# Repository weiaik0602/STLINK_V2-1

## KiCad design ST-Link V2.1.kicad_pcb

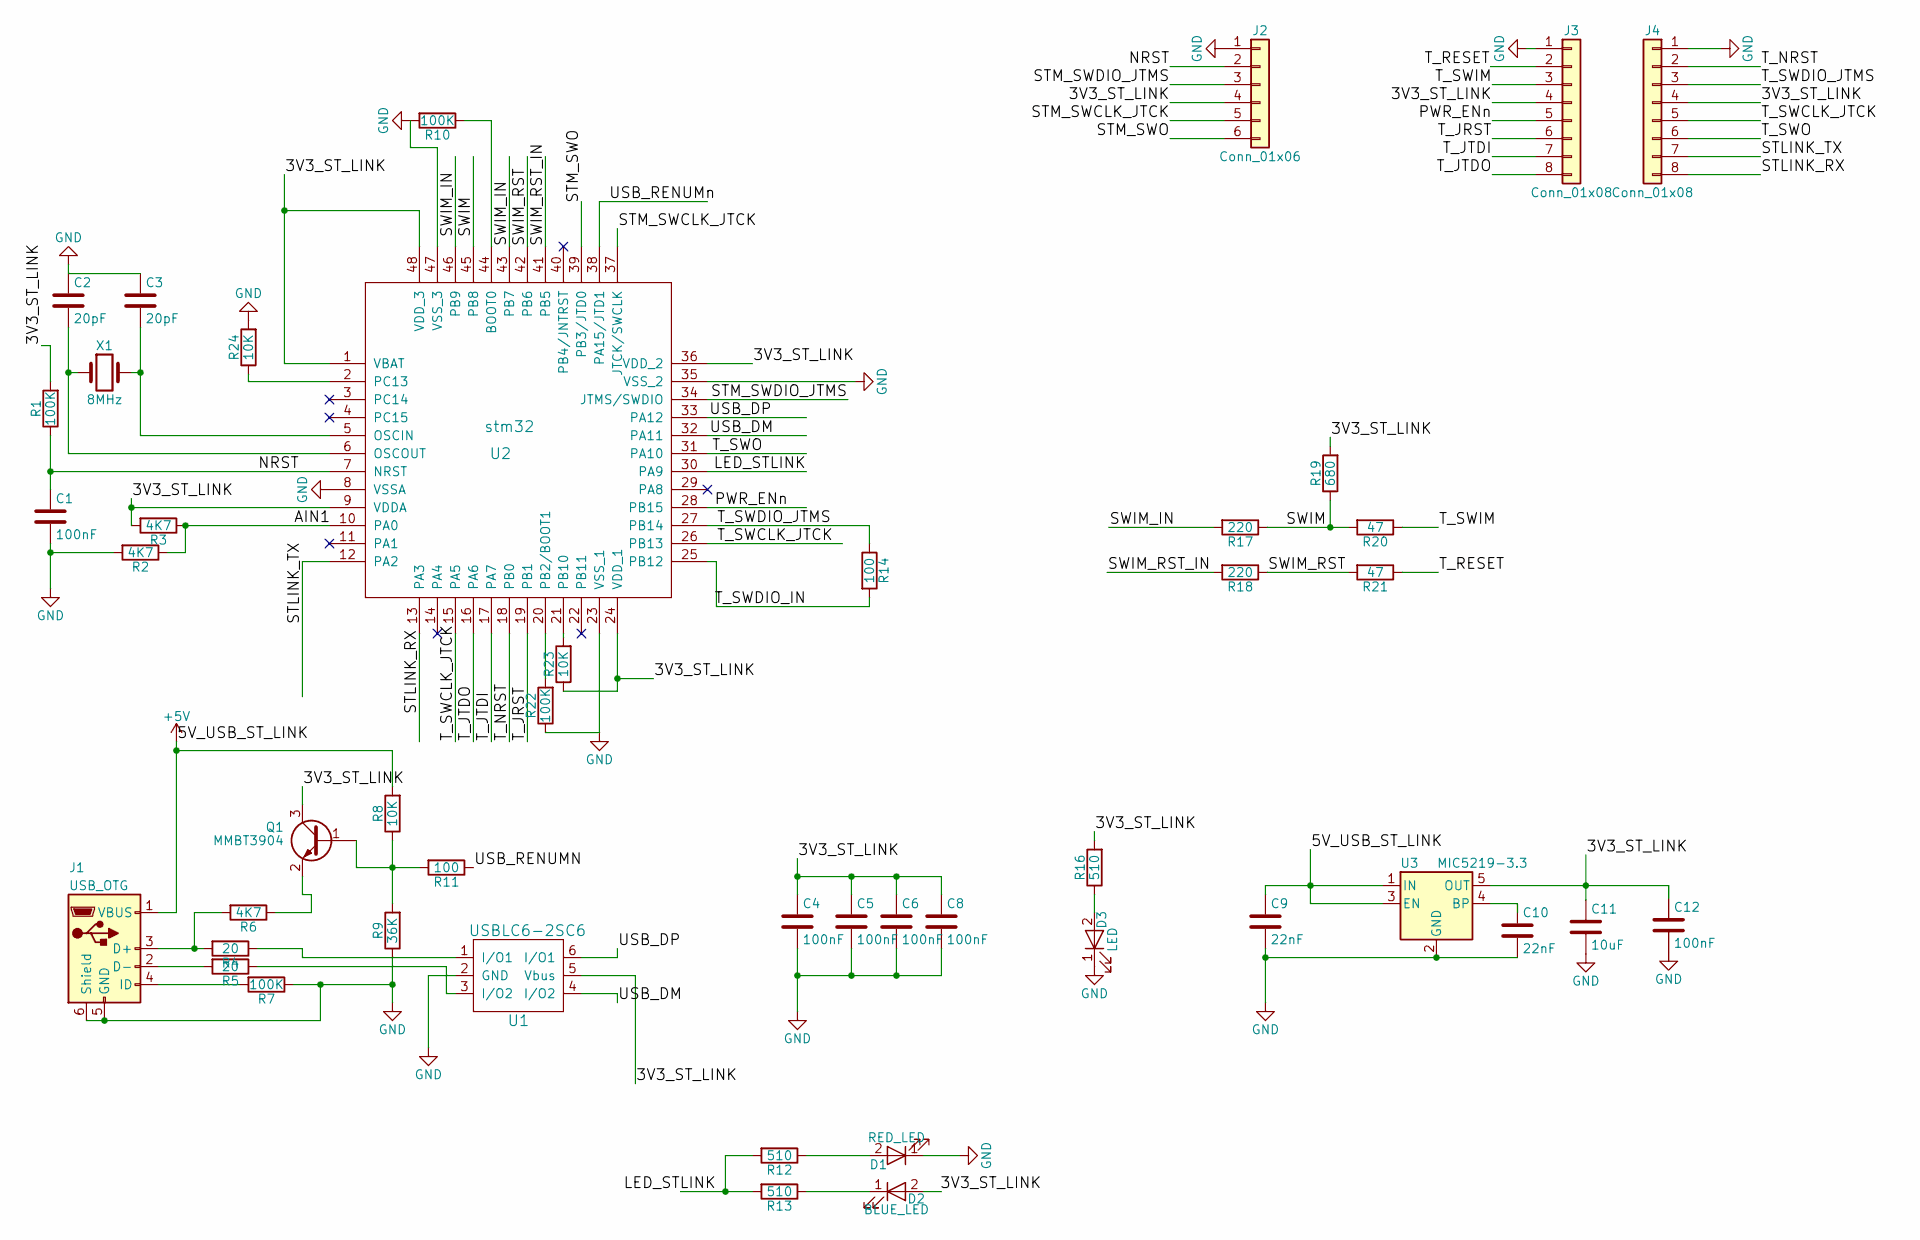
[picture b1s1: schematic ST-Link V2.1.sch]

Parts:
C1, C4, C5, C6, C8, C12: 100nF; C_0603
C2, C3: 20pF; C_0603
C9, C10: 22nF; C_0603
C11: 10uF; C_0603
D1: RED_LED; LED_0805
D2: BLUE_LED; LED_0805
D3: LED; LED_0805
J1: USB_OTG; USB_Micro-B_Molex-105017-0001
J2: Conn_01x06; Socket_Strip_Straight_1x06_Pitch2.54mm
J3, J4: Conn_01x08; METAL_PAD
Q1: MMBT3904; SOT-23
R1, R7, R10, R22: 100K; R_0603
R2, R3, R6: 4K7; R_0603
R4, R5: 20; R_0603
R8, R23, R24: 10K; R_0603
R9: 36K; R_0603
R11, R14: 100; R_0603
R12, R13, R16: 510; R_0603
R17, R18: 220; R_0603
R19: 680; R_0603
R20, R21: 47; R_0603
U1: USBLC6-2SC6; SOT-23-6
U2: stm32; UFQFPN48
U3: MIC5219-3.3; SOT-23-5
X1: 8MHz; Crystal_HC49-4H_Vertical

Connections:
+5V: C9.1, J1.1 (VBUS), R8.2, U3.1 (IN), U3.3 (EN)
/3V3_ST_LINK: C4.1, C5.1, C6.1, C8.1, C11.1, C12.1, D2.2 (A), J2.4, J3.4, J4.4, Q1.3 (C), R1.2, R3.2, R16.2, R19.2, R23.1, U1.5 (Vbus), U2.1 (VBAT), U2.9 (VDDA), U2.24 (VDD_1~), U2.36 (VDD_2~), U2.48 (VDD_3~), U3.5 (OUT)
/AIN1: R2.1, R3.1, U2.10 (PA0)
/LED_STLINK: R12.2, R13.2, U2.30 (PA9~)
/NRST: C1.1, J2.2, R1.1, U2.7 (NRST)
/PWR_ENn: J3.5, U2.28 (PB15~)
/STLINK_RX: J4.8, U2.13 (PA3~)
/STLINK_TX: J4.7, U2.12 (PA2)
/STM_SWCLK_JTCK: J2.5, U2.37 (JTCK/SWCLK~)
/STM_SWDIO_JTMS: J2.3, U2.34 (JTMS/SWDIO~)
/STM_SWO: J2.6, U2.39 (PB3/JTD0~)
/SWIM: R17.1, R19.1, R20.2, U2.45 (PB8~)
/SWIM_IN: R17.2, U2.43 (PB7~), U2.46 (PB9~)
/SWIM_RST: R18.1, R21.2, U2.42 (PB6~)
/SWIM_RST_IN: R18.2, U2.41 (PB5~)
/T_JRST: J3.6, U2.19 (PB1~)
/T_JTDI: J3.7, U2.17 (PA7~)
/T_JTDO: J3.8, U2.16 (PA6~)
/T_NRST: J4.2, U2.18 (PB0~)
/T_RESET: J3.2, R21.1
/T_SWCLK_JTCK: J4.5, U2.15 (PA5~), U2.26 (PB13~)
/T_SWDIO_IN: R14.2, U2.25 (PB12~)
/T_SWDIO_JTMS: J4.3, R14.1, U2.27 (PB14~)
/T_SWIM: J3.3, R20.1
/T_SWO: J4.6, U2.31 (PA10~)
/USB_DM: U1.4 (I/O2), U2.32 (PA11~)
/USB_DP: U1.6 (I/O1), U2.33 (PA12~)
/USB_RENUMN: R11.1, U2.38 (PA15/JTD1~)
GND: C1.2, C2.1, C3.1, C4.2, C5.2, C6.2, C8.2, C9.2, C10.2, C11.2, C12.2, D1.1 (K), D3.1 (K), J1.5 (GND), J1.6 (Shield), J2.1, J3.1, J4.1, R2.2, R7.1, R9.1, R10.2, R22.1, R24.2, U1.2 (GND), U2.0, U2.8 (VSSA), U2.23 (VSS_1~), U2.35 (VSS_2~), U2.47 (VSS_3~), U3.2 (GND)
unnamed: C2.2, U2.6 (OSCOUT), X1.1
unnamed: C3.2, U2.5 (OSCIN), X1.2
unnamed: C10.1, U3.4 (BP)
unnamed: D1.2 (A), R12.1
unnamed: D2.1 (K), R13.1
unnamed: D3.2 (A), R16.1
unnamed: J1.2 (D-), R5.2
unnamed: J1.3 (D+), R4.2, R6.2
unnamed: J1.4 (ID), R7.2
unnamed: Q1.1 (B), R8.1, R9.2, R11.2
unnamed: Q1.2 (E), R6.1
unnamed: R4.1, U1.1 (I/O1)
unnamed: R5.1, U1.3 (I/O2)
unnamed: R10.1, U2.44 (BOOT0~)
unnamed: R22.2, U2.20 (PB2/BOOT1~)
unnamed: R23.2, U2.21 (PB10~)
unnamed: R24.1, U2.2 (PC13)

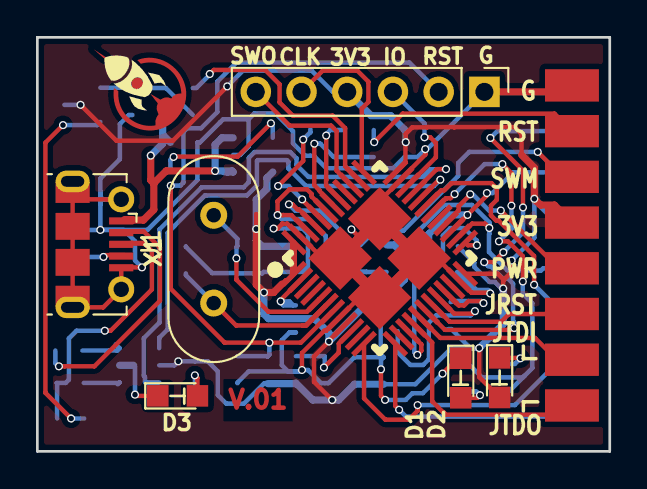
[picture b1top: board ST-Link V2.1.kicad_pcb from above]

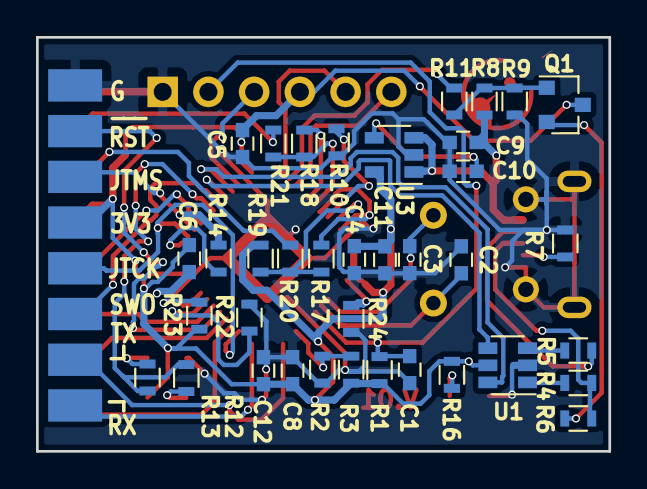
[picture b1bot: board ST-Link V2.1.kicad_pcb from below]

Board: 2 copper layers, 31.8 x 23.0 mm, 49 parts (38 on the bottom side), 46 nets.

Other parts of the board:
Dot: G***; Dot
HS_Crystal: G***; HS_Crystal
RocketCircle: G***; RocketCircle

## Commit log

2017-10-02 1st commmit
2017-10-03 drawing schematic
2017-10-03 continue schematic
2017-10-04 left usb and power part schematic
2017-10-04 still the same
2017-10-05 questions
2017-10-05 can start footprint
2017-10-09 waiting
2017-10-10 ALLIGNING
2017-10-11 ROUTE RESISTOR
2017-10-11 left abit
2017-10-12 done routing
2017-10-12 working footprint(need to reroute)
2017-10-13 routing
2017-10-13 left 3v3 and gnd
2017-10-17 routing all done (33.5mm X 21.1mm)
2017-10-20 save for reroute
2017-10-23 route route route
2017-10-24 left 3.3 & gnd
2017-10-24 still gt little bit
2017-10-27 minor changes
2017-10-30 las version need checking
2017-10-30 added label
2017-11-05 added 1C1R
2017-11-06 commit for deletion unused vias n tracks
2017-11-07 changed the Stm layout
2017-11-07 checked schematic
2017-11-13 need to change the footprint of the led
2017-11-15 added BOM,updated size and gerber file
2017-11-15 changed the size to eco user and adjusted the size of text
2017-11-17 changed the footprint of the U2
2017-11-18 changed font and copper pour area
2017-11-19 reroute the USB part
2017-11-19 changed copper pour clearance
2017-11-21 left the usb footprint
2017-11-21 changed the usb footprint
2017-11-22 Changed TXT size
2017-11-22 changed text size and some tracks
2017-12-01 changed the footprint of mcu, added the rocketCircle logo and shift the position of the V.01
2017-12-01 changed the footprint of mcu
2017-12-03 Overlapping a silk layer onto the crystals
2017-12-18 change the footprint of the USB
2017-12-18 changed the position of the usb
